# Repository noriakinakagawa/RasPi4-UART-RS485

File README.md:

# RasPi4-UART-RS485
Raspberry Pi 4 のUART 5chをRS485に変換したコマンド式サーボモータを動かすための基板データ

## Raspberry Pi OSの場合
/boot/config.txt or /boot/firmware/config.txt

## Ubuntuの場合
/boot/firmware/usercfg.txt

以下を追加して保存・再起動  
dtoverlay=pi3-miniuart-bt  
dtoverlay=uart0  
dtoverlay=uart2  
dtoverlay=uart3  
dtoverlay=uart4  
dtoverlay=uart5  
//init_uart_clock=169600000 // for RasPi5
  
/dev/ttyAMA0~AMA4の5ポートでRS485通信が可能となります。

## 注意事項
RTS信号をTXDから遅延タイマICを介して生成しているため、汎用的に使う場合は考慮が必要です。

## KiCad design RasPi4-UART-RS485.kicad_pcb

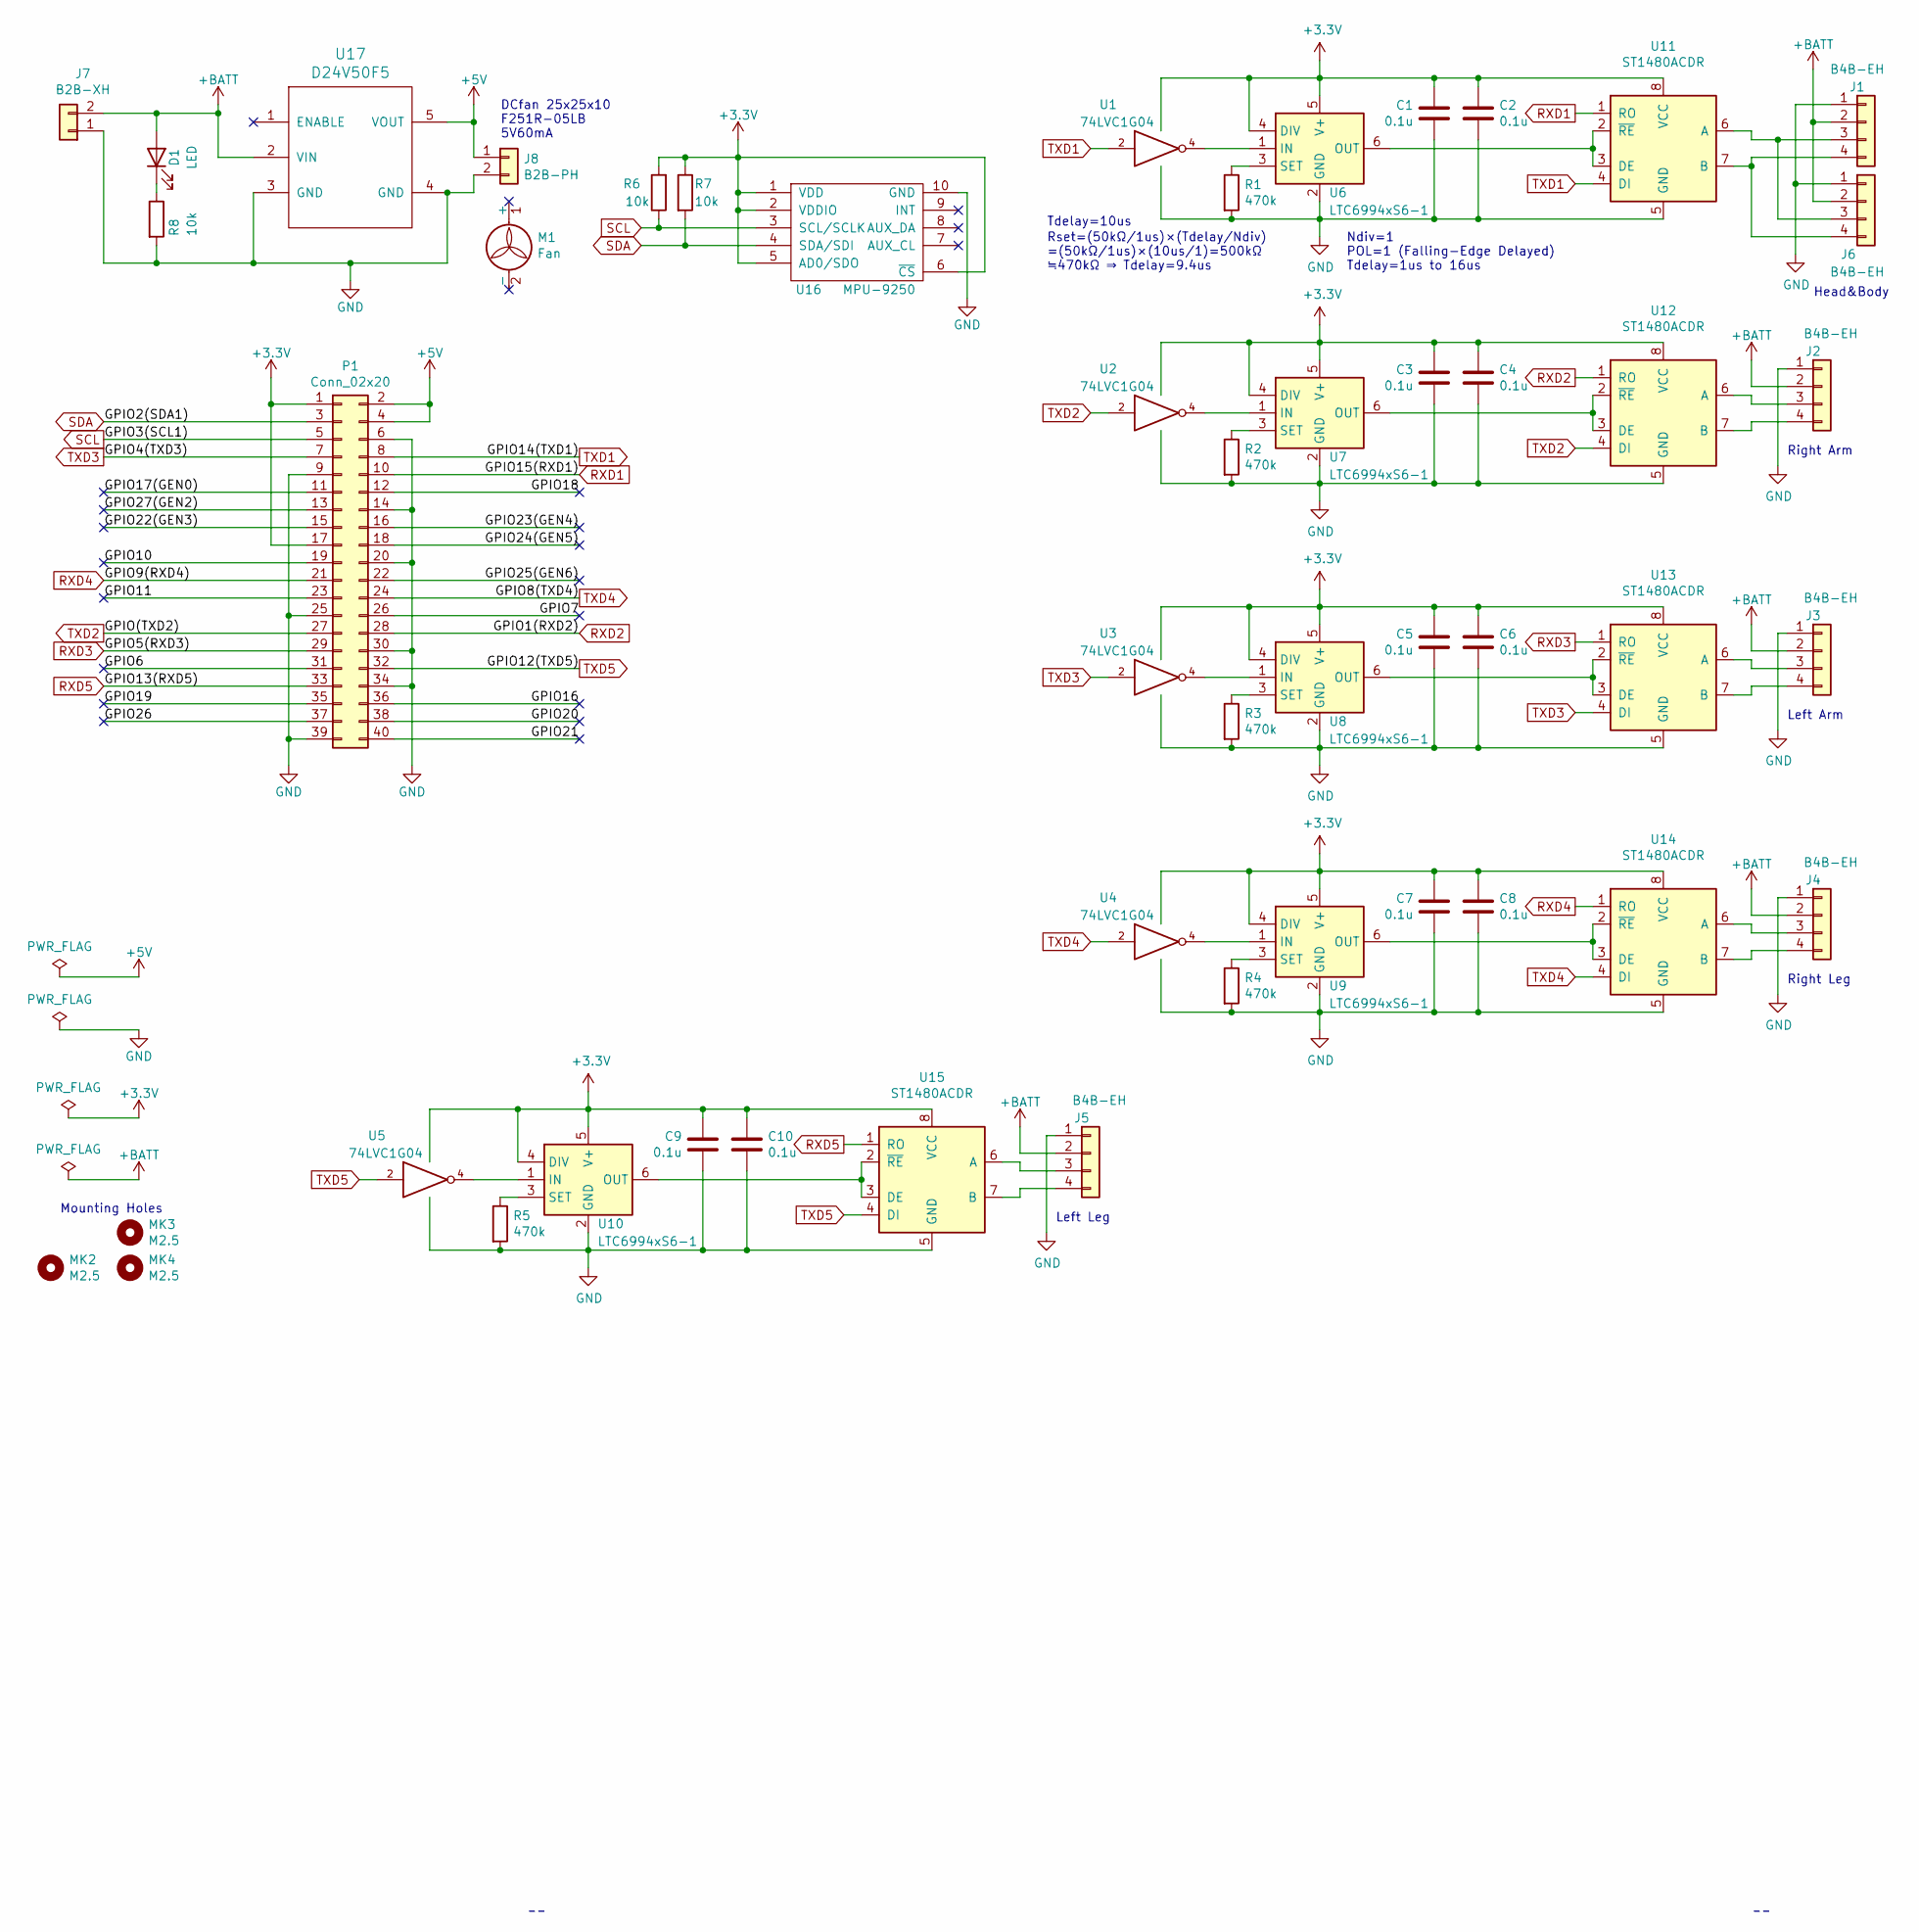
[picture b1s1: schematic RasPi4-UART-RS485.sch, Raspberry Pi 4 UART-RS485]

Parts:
C1, C2, C3, C4, C5, C6, C7, C8, C9, C10: 0.1u; C_0603
D1: LED; LED_0603
J1, J2, J3, J4, J5, J6: B4B-EH; JST_EH_B4B-EH-A_1x04_P2.50mm_Vertical
J7: B2B-XH; JST_XH_B2B-XH-A_1x02_P2.50mm_Vertical
J8: B2B-PH; JST_PH_B2B-PH-K_1x02_P2.00mm_Vertical
M1: Fan; F251R-05LB
MK2, MK3, MK4: M2.5; MountingHole_2.7mm_M2.5
P1: Conn_02x20; Socket_Strip_Straight_2x20_Pitch2.54mm
R1, R2, R3, R4, R5: 470k; R_0603
R6, R7, R8: 10k; R_0603
U1, U2, U3, U4, U5: 74LVC1G04; SOT-353_SC-70-5
U6, U7, U8, U9, U10: LTC6994xS6-1; TSOT-23-6
U11, U12, U13, U14, U15: ST1480ACDR; SOIC-8_3.9x4.9mm_Pitch1.27mm
U16: MPU-9250
U17: D24V50F5

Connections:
+3V3: C1.1, C2.1, C3.1, C4.1, C5.1, C6.1, C7.1, C8.1, C9.1, C10.1, P1.1, P1.17, R6.2, R7.1, U1.5 (VCC), U2.5 (VCC), U3.5 (VCC), U4.5 (VCC), U5.5 (VCC), U6.4 (DIV), U6.5 (V+), U7.4 (DIV), U7.5 (V+), U8.4 (DIV), U8.5 (V+), U9.4 (DIV), U9.5 (V+), U10.4 (DIV), U10.5 (V+), U11.8 (VCC), U12.8 (VCC), U13.8 (VCC), U14.8 (VCC), U15.8 (VCC), U16.1 (VDD), U16.2 (VDDIO), U16.5 (AD0/SDO), U16.6 (~CS)
+5V: J8.1, P1.2, P1.4, U17.5 (VOUT)
+BATT: D1.2 (A), J1.2, J2.2, J3.2, J4.2, J5.2, J6.2, J7.2, U17.2 (VIN)
/GPIO6: P1.31
/GPIO7: P1.26
/GPIO10: P1.19
/GPIO11: P1.23
/GPIO16: P1.36
/GPIO17(GEN0): P1.11
/GPIO18: P1.12
/GPIO19: P1.35
/GPIO20: P1.38
/GPIO21: P1.40
/GPIO22(GEN3): P1.15
/GPIO23(GEN4): P1.16
/GPIO24(GEN5): P1.18
/GPIO25(GEN6): P1.22
/GPIO26: P1.37
/GPIO27(GEN2): P1.13
GND: C1.2, C2.2, C3.2, C4.2, C5.2, C6.2, C7.2, C8.2, C9.2, C10.2, J1.1, J2.1, J3.1, J4.1, J5.1, J6.1, J7.1, J8.2, P1.6, P1.9, P1.14, P1.20, P1.25, P1.30, P1.34, P1.39, R1.2, R2.2, R3.2, R4.2, R5.2, R8.2, U1.3 (GND), U2.3 (GND), U3.3 (GND), U4.3 (GND), U5.3 (GND), U6.2 (GND), U7.2 (GND), U8.2 (GND), U9.2 (GND), U10.2 (GND), U11.5 (GND), U12.5 (GND), U13.5 (GND), U14.5 (GND), U15.5 (GND), U16.10 (GND), U17.3 (GND), U17.4 (GND)
unnamed: D1.1 (K), R8.1
unnamed: J1.3, J6.3, U11.6 (A)
unnamed: J1.4, J6.4, U11.7 (B)
unnamed: J2.3, U12.6 (A)
unnamed: J2.4, U12.7 (B)
unnamed: J3.3, U13.6 (A)
unnamed: J3.4, U13.7 (B)
unnamed: J4.3, U14.6 (A)
unnamed: J4.4, U14.7 (B)
unnamed: J5.3, U15.6 (A)
unnamed: J5.4, U15.7 (B)
unnamed: R1.1, U6.3 (SET)
unnamed: R2.1, U7.3 (SET)
unnamed: R3.1, U8.3 (SET)
unnamed: R4.1, U9.3 (SET)
unnamed: R5.1, U10.3 (SET)
unnamed: U1.4, U6.1 (IN)
unnamed: U2.4, U7.1 (IN)
unnamed: U3.4, U8.1 (IN)
unnamed: U4.4, U9.1 (IN)
unnamed: U5.4, U10.1 (IN)
unnamed: U10.6 (OUT), U15.2 (~RE~), U15.3 (DE)
unnamed: U6.6 (OUT), U11.2 (~RE~), U11.3 (DE)
unnamed: U7.6 (OUT), U12.2 (~RE~), U12.3 (DE)
unnamed: U8.6 (OUT), U13.2 (~RE~), U13.3 (DE)
unnamed: U9.6 (OUT), U14.2 (~RE~), U14.3 (DE)
RXD1: P1.10, U11.1 (RO)
RXD2: P1.28, U12.1 (RO)
RXD3: P1.29, U13.1 (RO)
RXD4: P1.21, U14.1 (RO)
RXD5: P1.33, U15.1 (RO)
SCL: P1.5, R6.1, U16.3 (SCL/SCLK)
SDA: P1.3, R7.2, U16.4 (SDA/SDI)
TXD1: P1.8, U1.2, U11.4 (DI)
TXD2: P1.27, U2.2, U12.4 (DI)
TXD3: P1.7, U3.2, U13.4 (DI)
TXD4: P1.24, U4.2, U14.4 (DI)
TXD5: P1.32, U5.2, U15.4 (DI)

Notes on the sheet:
Mounting Holes
Tdelay=10us
Rset=(50kΩ/1us)×(Tdelay/Ndiv) =(50kΩ/1us)×(10us/1)=500kΩ ≒470kΩ ⇒ Tdelay=9.4us
Ndiv=1 POL=1 (Falling-Edge Delayed) Tdelay=1us to 16us
Head&Body
Right Arm
Left Arm
Right Leg
Left Leg
DCfan 25x25x10 F251R-05LB 5V60mA

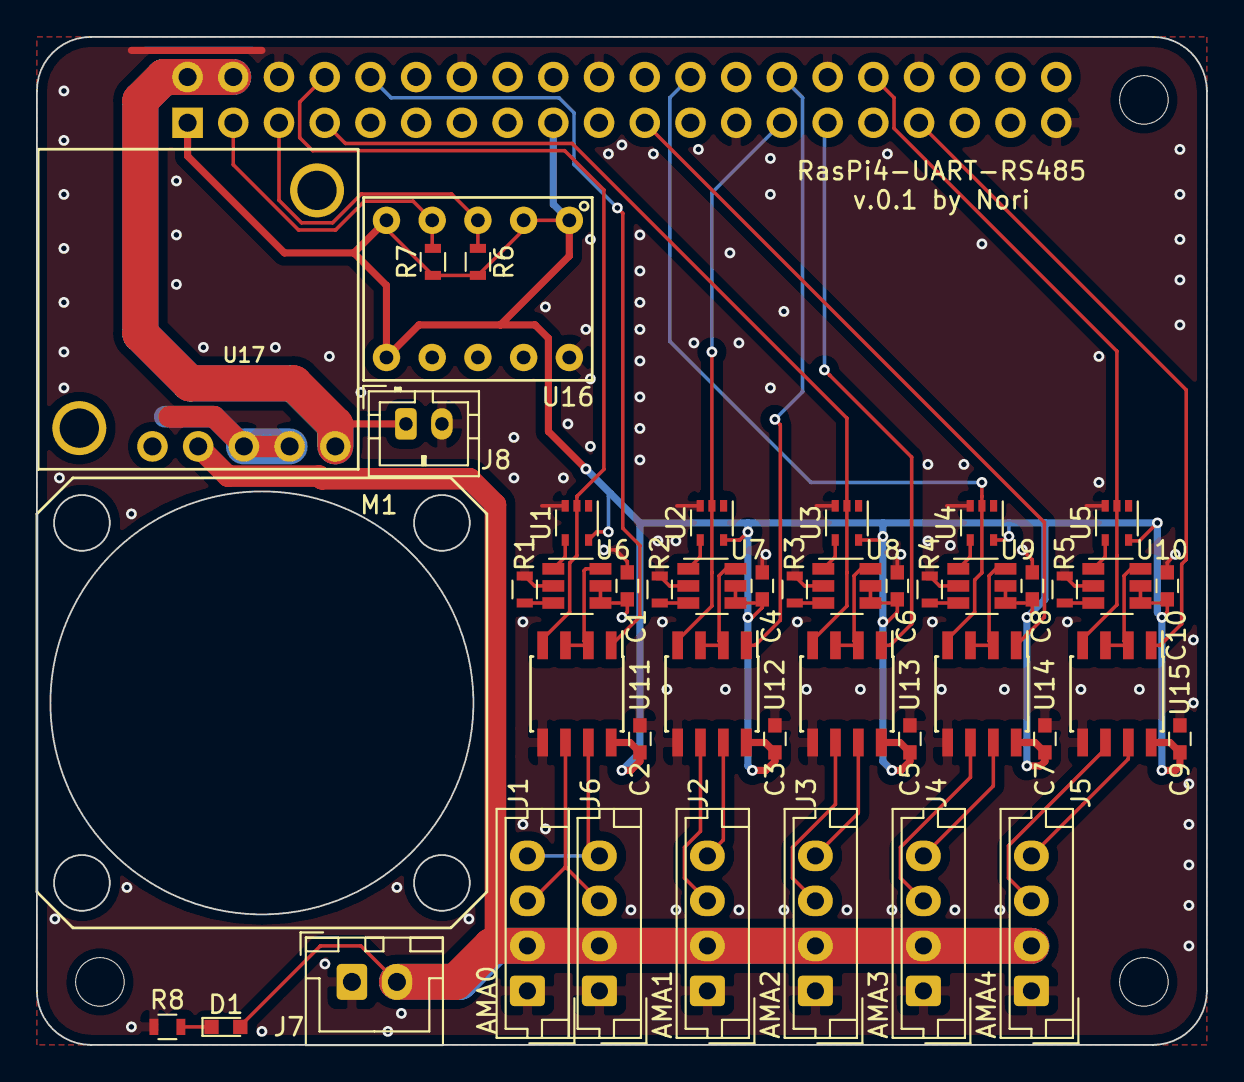
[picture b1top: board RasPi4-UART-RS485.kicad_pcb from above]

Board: 2 copper layers, 65.0 x 56.0 mm, 49 parts (1 on the bottom side), 42 nets.

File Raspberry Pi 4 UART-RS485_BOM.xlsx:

Reference | Quantity | Footprint | Datasheet | 購入URL | 型番 | 数量 | 購入先 | 製造数 | 5.0 | カゴチェック | 代替品を使う場合使わない部品
> C1-C10 | 0.1u | Capacitors_SMD:C_0603 | ~ | https://www.digikey.jp/product-detail/ja/kemet/C0603C104M4RA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 | C0603C104M4RACTU | 10.0 | Digi-key | 50
D1 | LED | LEDs:LED_0603 | ~ | https://www.digikey.jp/product-detail/ja/lite-on-inc/LTST-C1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 | LTST-C190KRKT | 1.0 | Digi-key | 5
> J1-J6 | B4B-EH | Connectors_JST:JST_EH_B4B-EH-A_1x04_P2.50mm_Vertical | ~ | https://www.digikey.jp/product-detail/ja/jst-sales-america-i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 | B4B-EH-A(LF)(SN) | 6.0 | Digi-key | 30
J7 | B2B-XH | Connectors_JST:JST_XH_B2B-XH-A_1x02_P2.50mm_Vertical | ~ | https://akizukidenshi.com/catalog/g/gC-12247/ | B2B-XH-A(LF)(SN | 1.0 | 秋月電子通商 | 5
J8 | B2B-PH | Connectors_JST:JST_PH_B2B-PH-K_1x02_P2.00mm_Vertical | ~ | https://akizukidenshi.com/catalog/g/gC-12802/ | B2B-PH-K-S(LF)(SN) | 1.0 | 秋月電子通商 | 5
M1 | Fan | F251R-05LB:F251R-05LB | ~ | https://www.digikey.jp/product-detail/ja/nidec-copal-electro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 | F251R-05LB | 1.0 | Digi-key | 5
M1 | Fan | 鉄＋なべBタイト |  | https://wilco.jp/products/F/FBP-N.html#page3 | FBP-0306N | 4.0 | ウィルコ | 20
MK2-MK4 | M2.6 | ジュラコンスペーサ |  | https://www.hirosugi-net.co.jp/shop/g/g3654/ | BS-2611E | 3.0 | ヒロスギネット | 15
MK2-MK4 | M2.6 | 鉄＋なべ小ねじ |  | https://wilco.jp/products/F/F-N.html#page3 | F-2606N | 3.0 | ウィルコ | 15
P1 | Conn_02x20 | Connector_PinSocket_2.54mm:PinSocket_2x20_P2.54mm_Vertical |  | https://akizukidenshi.com/catalog/g/gC-00085/ | FH-2x20SG | 1.0 | 秋月電子通商 | 5
> R1-R5 | 470k | Resistors_SMD:R_0603 | ~ | https://www.digikey.jp/product-detail/ja/panasonic-electroni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 | ERJ-3EKF4703V | 5.0 | Digi-key | 25
> R6-R8 | 10k | Resistors_SMD:R_0603 | ~ | https://www.digikey.jp/product-detail/ja/te-connectivity-pas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 | CRG0603F10K/10 | 3.0 | Digi-key | 15
> U1-U5 | 74LVC1G04 | TO_SOT_Packages_SMD:SOT-353_SC-70-5 | https://assets.nexperia.com/documents/data-sheet/74LVC1G04.pdf | https://www.digikey.jp/product-detail/ja/nexperia-usa-inc/74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 | 74LVC1G04GW,125 | 5.0 | Digi-key | 25
> U6-U10 | LTC6994xS6-1 | TO_SOT_Packages_SMD:TSOT-23-6 | https://www.analog.com/media/en/technical-documentation/data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 | https://www.digikey.jp/product-detail/ja/analog-devices-inc/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 | LTC6994CS6-1#TRMPBF | 5.0 | Digi-key | 25
> U11-U15 | ST1480ACDR | SMD_Packages:SOIC-8-N | https://media.digikey.com/pdf/Data%20Sheets/ST%20Microelectr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 | https://www.digikey.jp/product-detail/ja/stmicroelectronics/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 | ST1480ACDR | 5.0 | Digi-key | 25
U16 | MPU-9250 | MPU-9250:MPU-9250 | https://strawberry-linux.com/pub/mpu-9250-manual.pdf | https://strawberry-linux.com/catalog/items?code=12250 | MPU-9250 | 1.0 | ストロベリーリナックス | 5
U17 | D24V50F5 | D24V50F5:D24V50F5 | https://www.pololu.com/product/2851 | https://store.shopping.yahoo.co.jp/suzakulab/pololu-2851.html | D24V50F5 | 1.0 | 朱雀技研 | 5

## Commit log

2020-12-29 最初のアップロード
2020-12-29 Create LICENCE
2020-12-29 Rename LICENCE to LICENCE.md
2020-12-29 BOM uploard
